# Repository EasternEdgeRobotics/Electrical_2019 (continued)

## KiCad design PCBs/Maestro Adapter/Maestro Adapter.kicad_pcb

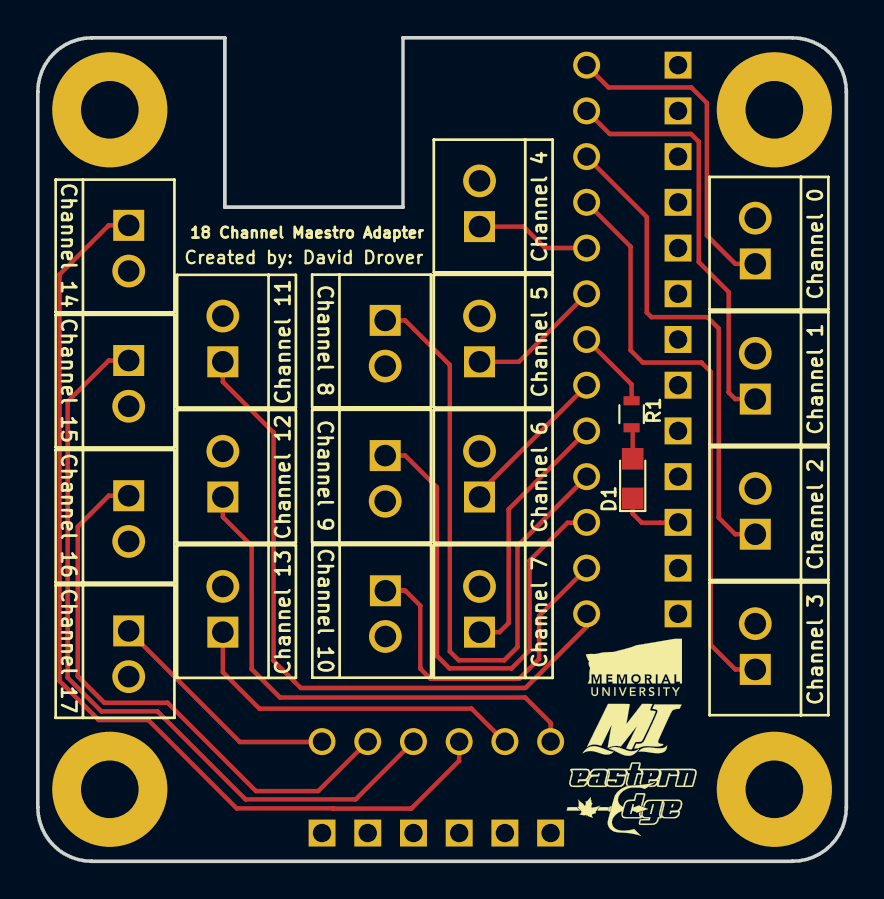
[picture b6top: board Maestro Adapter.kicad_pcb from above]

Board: 2 copper layers, 44.9 x 45.8 mm, 21 parts (0 on the bottom side), 21 nets.

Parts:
18 Channel Maestro: 18ChannelMaestro
Channel 0, Channel 1, Channel 2, Channel 3, Channel 4, Channel 5, Channel 6, Channel 7, Channel 8, Channel 9, Channel 10, Channel 11, Channel 12, Channel 13, Channel 14, Channel 15, Channel 16, Channel 17: 1x2_molex_llc
D1: LED; LED_0805
R1: R; R_0603

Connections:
+5V: 18 Channel Maestro.7, R1.1
GND: 18 Channel Maestro.20, 18 Channel Maestro.21, 18 Channel Maestro.22, 18 Channel Maestro.23, 18 Channel Maestro.24, 18 Channel Maestro.25, 18 Channel Maestro.26, 18 Channel Maestro.27, 18 Channel Maestro.28, 18 Channel Maestro.29, 18 Channel Maestro.30, 18 Channel Maestro.31, 18 Channel Maestro.32, 18 Channel Maestro.33, 18 Channel Maestro.34, 18 Channel Maestro.35, 18 Channel Maestro.36, 18 Channel Maestro.37, 18 Channel Maestro.38, Channel 0.2, Channel 1.2, Channel 2.2, Channel 3.2, Channel 4.2, Channel 5.2, Channel 6.2, Channel 7.2, Channel 8.2, Channel 9.2, Channel 10.2, Channel 11.2, Channel 12.2, Channel 13.2, Channel 14.2, Channel 15.2, Channel 16.2, Channel 17.2, D1.1
unnamed: D1.2, R1.2
unnamed: 18 Channel Maestro.1, Channel 0.1
unnamed: 18 Channel Maestro.2, Channel 1.1
unnamed: 18 Channel Maestro.12, Channel 10.1
unnamed: 18 Channel Maestro.13, Channel 11.1
unnamed: 18 Channel Maestro.14, Channel 12.1
unnamed: 18 Channel Maestro.15, Channel 13.1
unnamed: 18 Channel Maestro.16, Channel 14.1
unnamed: 18 Channel Maestro.17, Channel 15.1
unnamed: 18 Channel Maestro.18, Channel 16.1
unnamed: 18 Channel Maestro.19, Channel 17.1
unnamed: 18 Channel Maestro.3, Channel 2.1
unnamed: 18 Channel Maestro.4, Channel 3.1
unnamed: 18 Channel Maestro.5, Channel 4.1
unnamed: 18 Channel Maestro.6, Channel 5.1
unnamed: 18 Channel Maestro.8, Channel 6.1
unnamed: 18 Channel Maestro.9, Channel 7.1
unnamed: 18 Channel Maestro.10, Channel 8.1
unnamed: 18 Channel Maestro.11, Channel 9.1

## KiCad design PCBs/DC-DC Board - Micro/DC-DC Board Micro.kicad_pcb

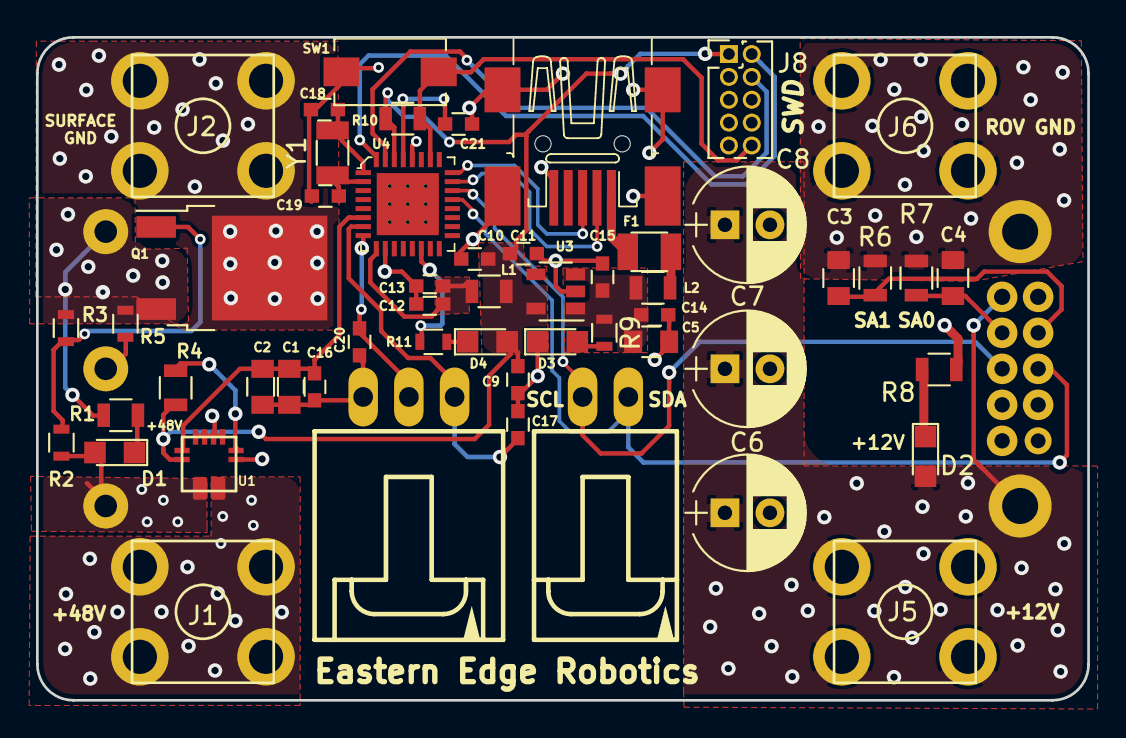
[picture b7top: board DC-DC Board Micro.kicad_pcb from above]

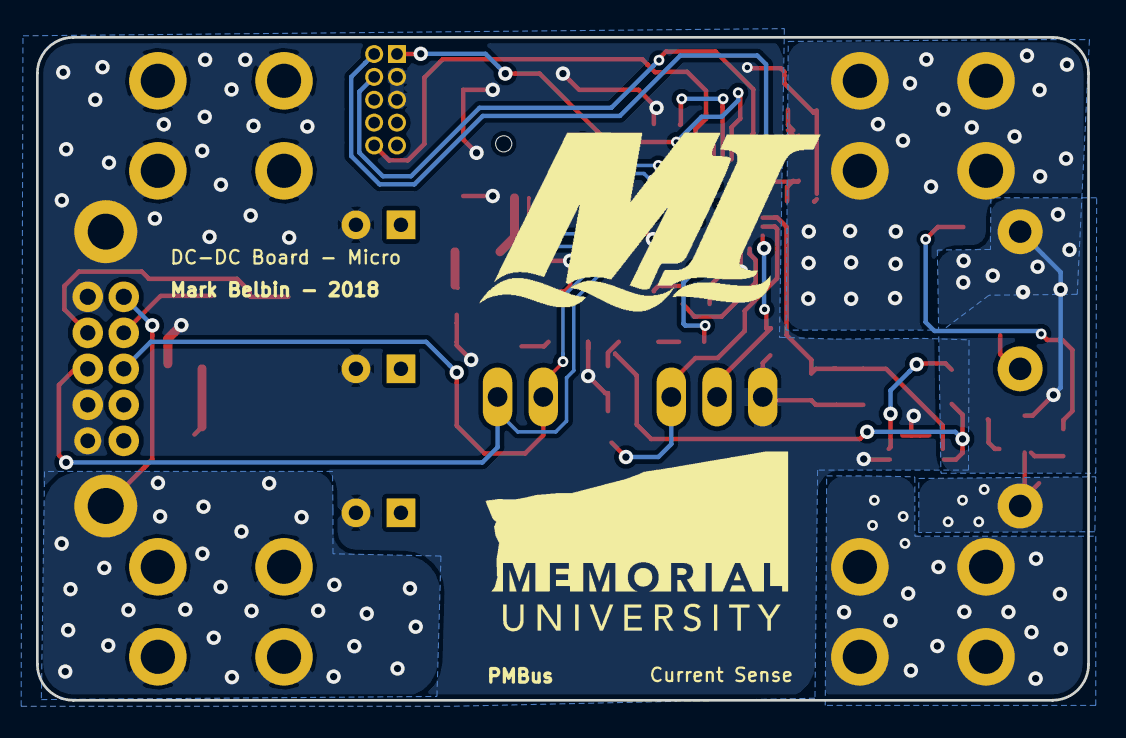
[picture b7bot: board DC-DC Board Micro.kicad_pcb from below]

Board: 2 copper layers, 58.4 x 36.8 mm, 56 parts (2 on the bottom side), 34 nets.

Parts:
C1, C5: 1uF; C_0805
C2: 0.1uF; C_0805
C3, C4: 4.7nF; C_0805
C6: 47uF; CP_Radial_D6.3mm_P2.50mm
C7, C8: 220uF; CP_Radial_D6.3mm_P2.50mm
C9, C12, C14: 10uF; C_0603
C10, C15, C16, C17, C20: 1uF; C_0603
C11, C13, C21: 0.1uF; C_0603
C18, C19: 22pF; C_0603
D1: GRN; LED_0805
D2: BLUE; LED_0805
D3: RED; LED_0805
D4: ORNGE; LED_0805
F1: 500mA; Fuse_SMD1206_Reflow
J1, J2, J5, J6: Conn_01x01; RingTerminal
J3: Conn_01x02; 70553-02
J4: Conn_01x03; 70553-03
J7: USB_B_Mini; 32005-201
J8: Conn_02x05_Odd_Even; Pin_Header_Straight_2x05_Pitch1.27mm
L1, L2: Ferrite_Bead; L_0805
Q1: Q_NMOS_GDS; TO-252-2
R1, R10: 10k; R_0805
R2: 698k; R_0603
R3: 200k; R_0603
R4, R8: 1k; R_0805
R5: 0; R_0603
R6, R7: 0; R_0805
R9: 330; R_0603
R11: 150; R_0603
SW1: SW_Push; SW_SPST_EVQPE1
U1: ACS711
U2: DBQ0135V2; MurataDC-DC
U3: TLV733P; SOT-23-5
U4: ATSAMD21E16L-MFT; QFN-32-1EP_5x5mm
U$15: MUNLOGO
U$16: MILOGO
Y1: 32.7680kHz; Crystal_SMD_3215-2pin_3.2x1.5mm

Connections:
3V3_FILT: C12.1, C13.1, L1.1, U4.9
+3V3: C9.1, C10.1, C11.1, D4.2, J8.1, L1.2, R4.1, R10.1, U1.12, U3.5, U4.30
+5V: C5.1, C14.1, C15.1, L2.1, R9.1, U3.1, U3.3
+12V: C6.1, C7.1, C8.1, D2.2, J5.1, U2.6, U2.16
/+48V: J1.1, U1.3
Earth: Q1.3, R1.2, R3.2, R5.2, U2.4
GND: C1.2, C2.2, C3.2, C4.2, C5.2, C6.2, C7.2, C8.2, C9.2, C10.2, C11.2, C12.2, C13.2, C14.2, C15.2, C16.2, C17.2, C18.2, C19.2, C20.2, C21.2, D3.1, J4.3, J6.1, J7.5, J7.6, J8.3, J8.5, R6.2, R7.2, R8.2, SW1.1, U1.5, U1.7, U2.5, U2.7, U2.13, U2.15, U3.2, U4.10, U4.28
unnamed: C3.1, R6.1, U2.9
unnamed: C4.1, R7.1, U2.8
unnamed: C18.1, U4.1, Y1.1
unnamed: C19.1, U4.2, Y1.2
unnamed: C21.1, U4.29
unnamed: D1.1, R1.1
unnamed: D1.2, R2.1, U1.1, U2.1
unnamed: D2.1, R8.1
unnamed: D3.2, R9.2
unnamed: D4.1, R11.2
unnamed: F1.1, J7.1
unnamed: F1.2, L2.2
unnamed: J2.1, Q1.2
unnamed: Q1.1, R2.2, R3.1
unnamed: R4.2, U1.6
unnamed: R5.1, U2.2
unnamed: R11.1, U4.14
SCL: J3.2, U2.10, U4.22
SDA: J3.1, U2.11, U4.21
SWCLK: J8.4, U4.31
SWDIO: J8.2, U4.32
USB+: J7.3, U4.24
USB-: J7.2, U4.23
VIOUT1: C1.1, C2.1, C16.1, U1.11, U4.6
VIOUT2: C17.1, J4.1, U4.7
VIOUT3: C20.1, J4.2, U4.8
~RESET~: J8.10, R10.2, SW1.2, U4.26

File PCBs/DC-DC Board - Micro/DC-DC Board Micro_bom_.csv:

Component,Description,Part,References,Value,Footprint,Quantity Per PCB,Datasheet,Status
1,Unpolarized capacitor,C,C11 C13 C21,0.1uF,C_0603,3,1276-1258-1-ND,
2,Unpolarized capacitor,C,C2,0.1uF,C_0805,1,399-1169-1-ND,
3,Unpolarized capacitor,C,C9 C12 C14,10uF,C_0603,3,490-7201-1-ND,
4,Unpolarized capacitor,C,C1 C5,1uF,C_0805,2,399-1284-1-ND,
5,Unpolarized capacitor,C,C10 C15 C16 C17 C20,1uF,C_0603,5,1276-6524-1-ND,
6,Polarised capacitor,CP1,C7 C8,220uF,CP_Radial_D6.3mm_P2.50mm,2,399-13664-ND,
7,Unpolarized capacitor,C,C18 C19,22pF,C_0603,2,311-3925-1-ND,
8,Unpolarized capacitor,C,C3 C4,4.7nF,C_0805,2,399-9092-1-ND,
9,Polarised capacitor,CP1,C6,47uF,CP_Radial_D6.3mm_P2.50mm,1,399-13665-ND,
10,LED generic,LED,D2,BLUE,LED_0805,1,732-4982-1-ND,
11,LED generic,LED,D1,GRN,LED_0805,1,732-4983-1-ND,
12,LED generic,LED,D4,ORNGE,LED_0805,1,160-1413-1-ND,
13,LED generic,LED,D3,RED,LED_0805,1,732-4984-1-ND,
14,"Fuse, generic",Fuse,F1,500mA,Fuse_SMD1206_Reflow,1,507-1075-1-ND,
15,"Generic connector, single row, 01x01, script generated (kicad-library-utils/schlib/autogen/connector/)",Conn_01x01,J1 J2 J5 J6,Conn_01x01,RingTerminal,4,36-7770-ND,
16,"Generic connector, single row, 01x02, script generated (kicad-library-utils/schlib/autogen/connector/)",Conn_01x02,J3,Conn_01x02,70553-02,1,WM4900-ND,
17,"Generic connector, single row, 01x03, script generated (kicad-library-utils/schlib/autogen/connector/)",Conn_01x03,J4,Conn_01x03,70553-03,1,WM4901-ND,
18,"Generic connector, double row, 02x05, odd/even pin numbering scheme (row 1 odd numbers, row 2 even numbers), script generated (kicad-library-utils/schlib/autogen/connector/)",Conn_02x05_Odd_Even,J8,Conn_02x05_Odd_Even,Pin_Header_Straight_2x05_Pitch1.27mm,1,609-3712-ND,
19,USB Mini Type B connector,USB_B_Mini,J7,USB_B_Mini,32005-201,1,151-1206-1-ND,
20,Ferrite bead,Ferrite_Bead,L1 L2,Ferrite_Bead,L_0805,2,490-9706-1-ND,
21,Transistor N-MOSFET with substrate diode (general),Q_NMOS_GDS,Q1,Q_NMOS_GDS,TO-252-2,1,DMTH6004SK3-13DICT-ND,
22,Resistor,R,R5,0,R_0603,1,RMCF0603ZT0R00CT-ND,
23,Resistor,R,R6 R7,0,R_0805,2,RMCF0805FT22K0CT-ND,
24,Resistor,R,R1,10k,R_0805,1,RNCP0805FTD10K0CT-ND,
25,Resistor US symbol,R_US,R10,10k,R_0805,1,RNCP0805FTD10K0CT-ND,
26,Resistor,R,R4 R8,1k,R_0805,2,RNCP0805FTD1K00CT-ND,
27,Resistor,R,R3,200k,R_0603,1,RMCF0603JT200KCT-ND,
28,Resistor US symbol,R_US,R9,330,R_0603,1,RHM330DCT-ND,
29,Resistor US symbol,R_US,R11,680,R_0603,1,RHM680DCT-ND,
30,Resistor,R,R2,698k,R_0603,1,RMCF0603FT698KCT-ND,
31,"Push button switch, generic, two pins",SW_Push,SW1,SW_Push,SW_SPST_EVQPE1,1,401-1707-1-ND,
32,,ACS711,U1,ACS711,ACS711,1,620-1482-1-ND,
33,IC MCU 32BIT 64KB FLASH 48QFN,ATSAMD21E16L-MFT,U4,ATSAMD21E16L-MFT,QFN-32-1EP_5x5mm,1,1611-ATSAMD21E16L-MFTCT-ND,Active
34,,MurataDC-DC,U2,DBQ0135V2,MurataDC-DC,1,S5801-05-ND,
35,"200 mA Low Dropout Voltage Regulator, Fixed Output 1.8V, SOT-23-5",TLV70018_SOT23-5,U3,TLV733P,SOT-23-5,1,296-40673-1-ND,
36,Two pin crystal,Crystal,Y1,32.7680kHz,Crystal_SMD_3215-2pin_3.2x1.5mm,1,887-2605-1-ND,





Component Groups:,36
Component Count:,54
Fitted Components:,54
Number of PCBs:,1
Total components:,54
Schematic Version:,
Schematic Date:,
BoM Date:,2018-11-03 11:54:16 PM
Schematic Source:,D:\ROV 2019\Github\2019\PCBs\DC-DC Board - Micro\DC-DC Board Micro.sch
KiCad Version:,Eeschema (5.0.0)

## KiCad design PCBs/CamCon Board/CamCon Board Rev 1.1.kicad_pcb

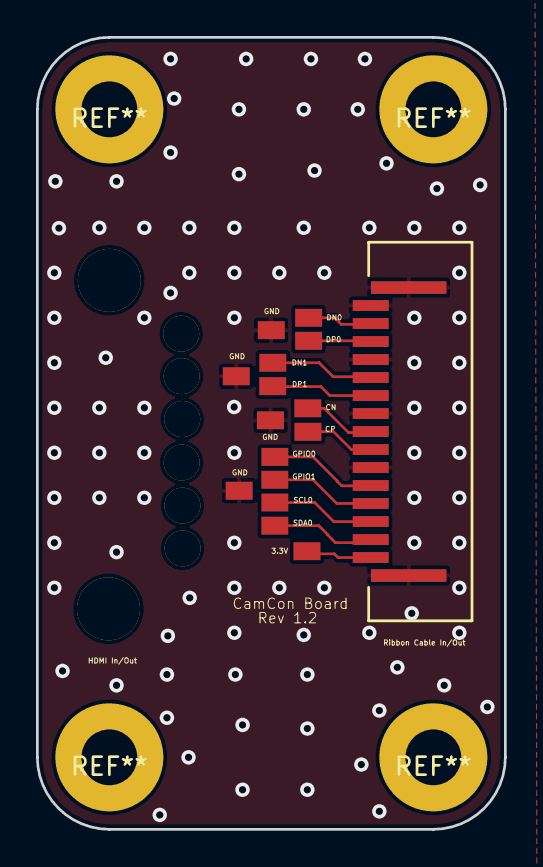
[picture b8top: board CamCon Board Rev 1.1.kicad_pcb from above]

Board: 2 copper layers, 26.0 x 44.0 mm, 25 parts (0 on the bottom side), 12 nets.

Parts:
@HOLE4, @HOLE5, @HOLE6, @HOLE7, @HOLE8, @HOLE9, @HOLE10, @HOLE11: (no value)
J1: SFW15R-1STE1LF; CON15_1X15_DRB_SFW
U$1, U$2, U$3, U$4, U$5, U$6, U$7, U$8, U$9, U$10, U$11, U$12, U$13, U$14, U$15: SOLDERPAD-CAMCON
U$12#2: EERLOGO

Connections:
GND: J1.1, J1.4, J1.7, J1.10, J1.16, J1.17, U$2.P$1, U$4.P$1, U$7.P$1, U$9.P$1
unnamed: J1.2, U$1.P$1
unnamed: J1.3, U$3.P$1
unnamed: J1.5, U$5.P$1
unnamed: J1.6, U$6.P$1
unnamed: J1.8, U$8.P$1
unnamed: J1.9, U$10.P$1
unnamed: J1.11, U$12.P$1
unnamed: J1.12, U$11.P$1
unnamed: J1.13, U$13.P$1
unnamed: J1.14, U$14.P$1
unnamed: J1.15, U$15.P$1

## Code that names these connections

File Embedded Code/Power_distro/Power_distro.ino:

/*************************************/
/*-----------------------------------*/
/**Power Distribution Embedded Code***/
/*****Eastern Edge Robotics 2019******/
/*-----------------------------------*/
/*************************************/

//Contributers: David Drover


//Pin Definitions
#define VIOUT1 2
#define VIOUT2 11
#define VIOUT3 3
#define VIOUT4 10
#define VIOUT5 4
#define VIOUT6 9
#define VIOUT7 5
#define VIOUT8 8
#define VIOUT9 6
#define VIOUT10 7
#define LED 14

float calculateCurrent(int channel, int channelNum);

char hold;
float zeroVoltage [10] = {1625.02,  //channel 1 zero amp voltage
                          1628.64,  //channel 2 zero amp voltage
                          1630.66,  //channel 3 zero amp voltage
                          1630.66,  //channel 4 zero amp voltage
                          1632.28,  //channel 5 zero amp voltage
                          1632.66,  //channel 6 zero amp voltage
                          1636.50,  //channel 7 zero amp voltage
                          1634.69,  //channel 8 zero amp voltage
                          1633.66,  //channel 9 zero amp voltage
                          1650.0}; //channel 10 zero amp voltage

void setup() 
{
  pinMode(VIOUT1, INPUT);
  pinMode(VIOUT2, INPUT);
  pinMode(VIOUT3, INPUT);
  pinMode(VIOUT4, INPUT);
  pinMode(VIOUT5, INPUT);
  pinMode(VIOUT6, INPUT);
  pinMode(VIOUT7, INPUT);
  pinMode(VIOUT8, INPUT);
  pinMode(VIOUT9, INPUT);
  pinMode(VIOUT10, INPUT);
  pinMode(LED, OUTPUT);
  Serial.begin(115200);
  analogReadResolution(12); // sets the ADC to 12 bit mode
}

void loop() 
{
  digitalWrite(LED, HIGH); //so LED won't start being on
  hold = Serial.read();
  while(hold == -1)
  {
    hold = Serial.read();
  }
  if(hold > -1 and hold < 255)
  {
    digitalWrite(LED, LOW); // signal data is starting to be sent
    
    //Serial.print("{ ");
    
    //Serial.print("fore-star-horz:");
    Serial.print(calculateCurrent(VIOUT1,1));
    
    //Serial.print(", fore-port-horz:");
    Serial.print(",");
    Serial.print(calculateCurrent(VIOUT2,2));
    
    //Serial.print(", fore-star-vert:");
    Serial.print(",");
    Serial.print(calculateCurrent(VIOUT3,3));
    
    //Serial.print(", aft-star-horz:");
    Serial.print(",");
    Serial.print(calculateCurrent(VIOUT4,4));
    
    //Serial.print(", fore-port-vert:");
    Serial.print(",");
    Serial.print(calculateCurrent(VIOUT5,5));
    
    //Serial.print(", aft-port-vert:");
    Serial.print(",");
    Serial.print(calculateCurrent(VIOUT6,6));
    
    //Serial.print(", aft-star-vert:");
    Serial.print(",");
    Serial.print(calculateCurrent(VIOUT7,7));
    
    //Serial.print(", aft-port-horz:");
    Serial.print(",");
    Serial.print(calculateCurrent(VIOUT8,8));
    
    //Serial.print(", PI/Switch/Tooling:");
    Serial.print(",");
    Serial.print(calculateCurrent(VIOUT9,9));

    //current chip not installed on pcb
    /*Serial.print(", Blank:");
    Serial.print(calculateCurrent(VIOUT10,10));*/
  
    //Serial.println(" }");
    
    delay(100);
    digitalWrite(LED, HIGH); //signals data is done being sent
  }
}


float calculateCurrent(int channel, int channelNum)
{
  int raw = analogRead(channel);
  float voltage = (raw / 4096.0) * 3300.0; // Gets you mV
  float amps = ((voltage - zeroVoltage[(channelNum - 1)]) / 45.0); //45mv/A
  return amps;
}

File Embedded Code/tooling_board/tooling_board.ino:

/*************************************/
/*-----------------------------------*/
/********Tooling Embedded Code********/
/*****Eastern Edge Robotics 2019******/
/*-----------------------------------*/
/*************************************/

// Contributers: David Drover

#include <Adafruit_Sensor.h> // imu
#include <Adafruit_BNO055.h> // imu
#include <utility/imumaths.h> // imu
#include "MS5837.h" // Pressure
#include <OneWire.h> // Temperature
#include <DallasTemperature.h>// Temperature
#include <Wire.h> // i2c
#include "wiring_private.h" // i2c

// Pin Definitions
#define VMetal 4
#define VPH A5
#define TempData 10
#define EnableA1 9
#define DirA1 14
#define EnableA2 15
#define DirA2 17
#define EnableB1 8
#define DirB1 16
#define EnableB2 19
#define DirB2 28
#define LED 18
#define LED_IN 11
#define SCL_Pin 23
#define SDA_Pin 22

// Global variables
int id;
int dir, dir1, dir2, dir3, dir4; 
int duty, duty1, duty2, duty3, duty4;
int LedDuty;
int tempPH = 0;
int mDetect = 0;
char buf[90];
char hold;
int x;
imu::Vector<3> euler; //primary sensors
imu::Vector<3> accel; //primary sensors
float Temp; //primary sensors
bool gyroSen = true; // Testing gyro
bool pressureSen = true; // Testing pressure
int motors[4] = {EnableA2, EnableB2, EnableA1, EnableB1}; //motors
int dirControl[4] = {DirA2, DirB2, DirA1, DirB1}; //motors
float temperature; // temperature sensor
int rawAvg; // pH sensor
float pH; // pH sensor

// Define one wire communication
OneWire oneWire(TempData);

// Define temperature sensor
DallasTemperature temp(&oneWire);

// Define pressure sensor
MS5837 sensor;

// Define Gyro sensor
Adafruit_BNO055 bno = Adafruit_BNO055();

void returnImuPressureData(int mode = 1);
void changeMotor(int motorNum, int dir, int duty);
void Led(int duty);
void returnSensorData(void);
float calculateTemp(void);
int metal(void);
float ph(double offset);

void setup(void) 
{
  pinPeripheral(11, PIO_TIMER_PWM);
  pinPeripheral(18, PIO_TIMER_PWM);
  pinPeripheral(19, PIO_TIMER_PWM);
  pinPeripheral(22, PIO_SERCOM);
  pinPeripheral(23, PIO_SERCOM);

  analogReadResolution(12); // Sets the ADC to 12 bit mode
  
  Serial.begin(115200);

  if(!sensor.init())
  {
    pressureSen = false;
  }
  
  sensor.setModel(MS5837::MS5837_02BA);
  sensor.setFluidDensity(997);
  
  if(!bno.begin())
  {
    gyroSen = false;
  }

  temp.begin();

  // Setup pins
  pinMode(VMetal, INPUT); 
  pinMode(VPH, INPUT); 
  pinMode(TempData, INPUT); 
  pinMode(EnableA1, OUTPUT);
  pinMode(DirA1, OUTPUT);
  pinMode(EnableA2, OUTPUT);
  pinMode(DirA2, OUTPUT);
  pinMode(EnableB1, OUTPUT);
  pinMode(DirB1, OUTPUT);
  pinMode(EnableB2, OUTPUT);
  pinMode(DirB2, OUTPUT);
  pinMode(LED, OUTPUT);
  pinMode(LED_IN, OUTPUT);
  
  // Ensure nothing run from not being set
  for(int i = 1; i<=4; i++)
  {
    changeMotor(i, 1, 0);
  }
  Led(0);
  for(int i = 0; i < 90; i++)
  {
    buf[i]= ',';
  }
}

void loop(void) 
{
  // Waiting for a serial write
  hold = Serial.read();
  while(hold == 255)
  {   
    if(tempPH == 1 or mDetect == 1)
    {
      returnSensorData();
    }
    else
    {
      if(gyroSen == false)
      {
        Serial.print("gyro not found");
        Serial.flush();
      }
      if(pressureSen == false)
      {
        Serial.print("pressure not found");
        Serial.flush();
      }
      returnImuPressureData();
    }
    hold = Serial.read(); 
  }

  // Serial reading code
  buf[0] = hold;
  x = 1;
  while(x <= 30 and hold != 255)
  {
    delay(4);
    hold = Serial.read();
    while( x == 0 and hold == 255)
    {
      hold = Serial.read();
    }
    buf[x] = hold;
    x++;
  }

  // Decides how to read the input and does the action

  if(buf[2] == 'm' and buf[7] == '1')
  {
    sscanf(buf, "{ motor1:%d, %d, motor2:%d, %d, motor3:%d, %d, motor4:%d, %d, LED:%d, sensorsreading:%d,%d }", &dir1, &duty1, &dir2, &duty2, &dir3, &duty3, &dir4, &duty4, &LedDuty, &tempPH , &mDetect);
    changeMotor(1, dir1, duty1);
    changeMotor(2, dir2, duty2);
    changeMotor(3, dir3, duty3);
    changeMotor(4, dir4, duty4);
    Led(LedDuty);
  }else if(buf[2] == 'm'){
    sscanf(buf, "{ motor:%d, %d, %d }", &id, &dir, &duty);
    changeMotor(id, dir, duty);
  }else if(buf[2] == 'L'){
    sscanf(buf, "{ LED:%d }", &LedDuty);
    Led(LedDuty);
  }else if(buf[2] == 's'){
    sscanf(buf, "{ sensorsreading:%d,%d }", &tempPH , &mDetect);
  }else{
    sscanf(buf, "%d,%d,%d,%d,%d,%d,%d,%d,%d,%d,%d", &dir1, &duty1, &dir2, &duty2, &dir3, &duty3, &dir4, &duty4, &LedDuty, &tempPH, &mDetect);
    changeMotor(1, dir1, duty1);
    changeMotor(2, dir2, duty2);
    changeMotor(3, dir3, duty3);
    changeMotor(4, dir4, duty4);
    Led(LedDuty);
  }
}


// Prints out imu and pressure sensors data
void returnImuPressureData(int mode)
{
  sensor.read();
  euler = bno.getVector(Adafruit_BNO055::VECTOR_EULER);
  accel = bno.getVector(Adafruit_BNO055::VECTOR_LINEARACCEL);
  Temp = bno.getTemp();

  Serial.print("P");
  Serial.flush();

  //Serial.print("Pressure:");
  Serial.print(",");
  Serial.flush();
  Serial.print(sensor.pressure());
  Serial.flush(); 
  
  //Serial.print(", TemperaturePS:"); 
  Serial.print(",");
  Serial.flush();
  Serial.print(sensor.temperature());
  Serial.flush(); 
 
  //Serial.print(", GyroX:");
  Serial.print(",");
  Serial.flush();
  Serial.print(euler.x());
  Serial.flush();
  
  //Serial.print(", GyroY:");
  Serial.print(",");
  Serial.flush();
  Serial.print(euler.y());
  Serial.flush();
  
  //Serial.print(", GyroZ:");
  Serial.print(",");
  Serial.flush();
  Serial.print(euler.z());
  Serial.flush();

  //Serial.print(", Accelx:");
  Serial.print(",");
  Serial.flush();
  Serial.print(accel.x());
  Serial.flush(); 

  //Serial.print(", Accely:");
  Serial.print(",");
  Serial.flush();
  Serial.print(accel.y());
  Serial.flush(); 

  //Serial.print(", Accelz:");
  Serial.print(",");
  Serial.flush();
  Serial.print(accel.z());
  Serial.flush(); 

  //Serial.print(", TemperatureIMU:");
  Serial.print(",");
  Serial.flush();
  Serial.println(Temp);
  Serial.flush();
}

// Changes motor turn speed
void changeMotor(int motorNum, int dir, int duty)
{
  //if(motorNum == 2)
  //{
  //  motorNum--;
  //  digitalWrite(dirControl[motorNum], dir);
  //  digitalWrite(motors[motorNum], (1.0*(duty/100.0)));
  //}
  //else
  //{
    motorNum--;
    digitalWrite(dirControl[motorNum], dir);
    analogWrite(motors[motorNum], (256.0*(duty/100.0)));
  //}
}

// Changes the brightness of the leds
void Led(int duty)
{
  duty = (256.0 *(duty / 100.0));
  analogWrite(LED, duty);
  analogWrite(LED_IN, (256 - duty));
}

// Prints out ph, metal and temperature sensor values
void returnSensorData(void)
{
  Serial.print("S");
  Serial.flush();
  
  //Serial.print("temperature:");
  Serial.print(",");
  Serial.flush();
  if(tempPH == 1)
  {
    Serial.print(calculateTemp());
    Serial.flush();
  }else{
    Serial.print("F");
    Serial.flush();
  }
  
  //Serial.print(", Metal:");
  Serial.print(",");
  Serial.flush();
  if(mDetect == 1)
  {
    Serial.print(metal());
    Serial.flush();
  }else{
    Serial.print("F");
    Serial.flush();
  }
  
  //Serial.print(", PH:");
  Serial.print(",");
  Serial.flush();
  if(tempPH == 1)
  {
    Serial.println(ph(2.72));
    Serial.flush();
  }else{
    Serial.println("F");
    Serial.flush();
  }
}

// Calculates temperature
float calculateTemp(void)
{
  delay(40);
  temp.requestTemperatures();
  delay(40);
  temperature = temp.getTempCByIndex(0);
  return temperature;
}

// Says if it is metal or not
int metal(void)
{
  if(analogRead(VMetal) < 100 )
  {
    return 1;
  }
  else
  {
    return 0;    
  }  
}

// Calculates ph level
float ph(double offset)
{
  rawAvg = 0;
  for( int i = 0; i < 4; i++)
  {
    rawAvg += analogRead(VPH);
    delay(5);
  }
  rawAvg /= 4;
  pH = ((3.5 * (rawAvg * (3.3 / 4096.0))) + offset);
  return pH;
}

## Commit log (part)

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2018-09-23 Added Bar02 Files
    Blue Robotics open-sourced their Bar02 PCB files. We could use this to reduce the Bar02 cost by over half
2018-09-23 Added CamCon Board PCB
    This board, which will be improved upon a little further, will serve as a bridge between the Pi's ribbon cables and an HDMI cable.
2018-09-23 Update README.md
    Added mention of PCBs
2018-09-24 Added Legacy Junction Box
    Added all my Junction Box stuff since it might come in handy
2018-09-24 Added BR Bar02 Library
    Arduino library for the pressure sensor in the Bar02. We can easily port this over to another micro when we need to, it's just a bunch of I2C commands.
2018-09-29 Played with 3D Models
    Tried out a few thngs with 3D models for components. Apparently the new KiCAD takes STEP files which is a huge time saver!!
2018-09-30 Cleaned up CamCon Board
2018-10-07 Started New CamCon Board
    Mostly sourced components and updated the EER library.
2018-10-07 Revert "Started New CamCon Board"
    This reverts commit b871feee2390acae07443b14e396deeaba97d5d0.
2018-10-07 Revert "Revert "Started New CamCon Board""
    This reverts commit 2fa29a33d9c013c2d74e11c9c642eee02ae13c05.
2018-10-07 Think everything's chill now
2018-10-07 Finished Mechanicals of the Dual CamCon Board
    Just need to do the routing now.
2018-10-08 Dual CamCon Board - Ready for Review
    Pretty much cleaned up this guy as much as I could. Needs to be reviewed by the team on a few different things.
    -FPC to HDMI legitness (will each pin line up) needs to be triple checked.
2018-10-10 Major Routing Fix for Dual CamCon
    After looking at the physical Pi Cam I realized that I had the pin map mirrored. I swapped the pins around on the FPC connector and cleaned up the board in general. Count this as a double check, stil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
2018-10-11 Touched up Dual CamCon
2018-10-13 Semi Final DC-DC Schematic
    Pretty much finalized the schematic and component selection for the no-micro version of the DC-DC board. The micro version will come later.
2018-10-15 DC-DC Board Final
    99% Done the first DC-DC Board. Just need to double check everything!!
2018-10-15 DC-DC Touchups
    Silk screen mostly
2018-10-16 Fixed DC-DC
    After looking at the IRL DC-DCs, I realized I had the footprint mirrored (the datasheet is not intuitive). I rerouted pretty much everything to fix it. RIP
2018-10-17 DC-DC Board DONE
    Should be done for sure now bys
2018-10-17 DC-DC Touchups
    Small layout touchups. Also double checked the reverse voltage protection in LTSpice, and it looks good!!! <1W of power dissipation!!
2018-10-19 Cleaned up BOM
    KiCAD has a built in BOM!! Woohooo!!!
2018-10-20 Started DC-DC with Micro
    Picked out microcontroller maybe? Still gotta decide if I want to use the 5x5 vs the 7x7.
2018-10-20 Added Datasheets
    Figured this would be useful to have on the Github
2018-10-20 Started Blank Project
    Commit all you can guys, also pull down what's been done.
2018-10-20 Added Blank Project
    Commit, commit, commit!!
2018-10-20 Added Blank Project
    Commit boyz
2018-10-21 DC-DC Mirco Updates
2018-10-22 DC-DC Boards 99%
    Both boards are pretty much done. They just need a few double checks and some BOM work has to be done for the Micro Board.
2018-10-23 DC-DC Micro Touchups
    Cleaned up layout and fixed orange test LED current limiting resistor.
2018-10-23 finished rough draft of Maestro Adapter
    3d model and EER silkscreen is done.
2018-10-23 added spot for missed gap in servo channels
    missed a gap between channel 5 and 6. so added additional pads
2018-10-24 Added Colour to 3D Model
    We probably have to change the footprint again anyways, but at least now its in colour!!!
2018-10-24 DC-DC Micro FINAL*
    Checked it over fully, gonna call this board finished now unless anyone else has a concern!
2018-10-24 Added another 3d model path
2018-10-25 Converting to 18 channel maestro
2018-10-25 Finished pcb Layout
2018-10-25 Finished traces
2018-10-26 Changed the mounting holes
2018-10-26 Revert "DC-DC Micro FINAL*"
    This reverts commit 0ab9bedbdf57a5134aa5828bf11276fde0e8bb90.
2018-10-26 Edited Paths for 3D Models
    This might fix an issue me and Patrick found. The paths for 3D models were absolute referenced as if it were on my computer. It's obviously fine for me, but not for everyone else loll. Hopefully the 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
2018-10-26 Move maestro to the bottom and move connectors
2018-10-26 added relative path for 3d models
2018-10-27 Added traces and rounded corners
    mounting hole centers are 4mm from the side
2018-10-27 Started Power Distro Board
    Started the schematic of the power distribution board (12V and GND bus). This will mostly be copy/paste, the hard part will come in the layout.
2018-10-27 Added EER logo silkscreen
2018-10-27 Added led and resistor pads
2018-10-27 Added text EER and year
2018-10-27 Schematic Finalized
    99% done on the schematic, just needs to be checked over and touched-up.
2018-10-29 BOM Finished Pwr Distro
    Finished the BOM (Bill of Materials) for the Power Distribution Board. Also the schematic is finalized for sure.
2018-10-29 Initial Component Position PD
    Placed initial component position. I'm going to bed.
2018-10-31 Small Tweaks
    3D Model for RPi GPIO on the CamCon was wrong.
2018-11-03 Updated Silkscreen PD
    Still need to check over the layout one last time, but she should be good to go.
2018-11-03 I'm sorry Keith
    It had to be done....
2018-11-03 finished motor driver circuit
2018-11-03 Finished PD Board
    All done!
2018-11-03 Started Relay
    finish relay values
2018-11-03 BOM Work
2018-11-03 Gerber Generation
    Oops should not have done this in the actuator branch but here we are loll. Just exported the gerber files for the DCDC / DCDC Micro & the PD Board. Should not affect what you guys are doing.
2018-11-04 Added CamCon Gerbers
    Need to fix these up loll
2018-11-04 Gerbers and Maestro Fix
    Added Gerbers for the maestro and fixed up the silkscreen.
2018-11-04 Minor Updates
    Trying to sneak these Power PCBs through PCBWay, they caught me on a few 0.2mm drills so I made em 0.3. We'll see if my 0.2mm clearance passes their 8mil clearance (0.2035mm)
2018-11-04 Added motor diver schematic and relay footprint
2018-11-04 More Gerbers
2018-11-04 Filled in some information about transistor
2018-11-08 3D Modeling
2018-11-10 reset accidental commit to master
2018-11-12 Updated Mirco Stuff
    Dodged a bullet
2018-11-14 added datasheets to H bridge compoents
2018-11-24 add wiki link to readme for docs
2018-11-25 Created project
2018-11-27 First SAMD21 Program!!
    Using Atmel Studio 7 here since it was the easist to get up and running. Gonna try and program this completely through the Arduino IDE eventually. pls help :)
2018-11-28 Arduino Test
    Got the board working with the Ardunio IDE. Still some testing we gotta do to check if it'll do everything we want (I2C, proper USB communication, analog in / digital out) Promising though :)
2018-12-08 PMBus Works!!
    Got the PMBus working on the DC-DC converters. I'll start making the commands more formalized. The only thing now is to figure out addresses. Worst case scenerio is we can't access 1-2 of the convert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
2019-01-18 Moved Repositories
    Moved my old branch in 2019 repo to this branch.
2019-01-18 Add unedited pressure and imu test code
2019-01-25 Initial Tooling Board
    - Created Project
    - Added Micro Schematic
    - Need to finalize everything else (I'm in for a long night)
2019-01-26 Add DC Motor Control
    -Added H-bridge drivers and logic inverters
    -Should be able to control up to 6 DC motors / other loads
    -We'll see if we can fit 3 chips on the board (we should be able to)
2019-01-26 Finished Actuator Section
    -Added Dual LED Control
    -Spec'd fets for nmos in LED circuit
    -Still need to map all control pins
2019-01-26 Added Sensors
    -Added pH Circuit and spec'd components
    -Added Pressure sensor connecter
    -Added External Temp sensor connector
    -Added metal detector connector + input circuit
    Need to add IMU interface now (not hard)
2019-01-26 Pins are Mapped
    -This was really difficult and it may not work.
    -We're gonna try it and see what works.
    -If it fails the next PCB will use arduino atmega chips since the open source libraries exist for them
    -Might do a combination of SAMD and atmega lol
    -God damn chinese new year
2019-01-26 Added Footprints
    -Whoooo boy here we go
2019-01-26 Removed 3rd DC Motor Driver
    -Can only do 4 DC motors now, not enough board space
2019-01-27 Almost Finished
    -Still going, help
2019-01-27 Just the Micro
    -Need to fricken route the micro help
2019-01-28 Tooling Board Finalized
    -Checked Routing
    -Added 3D models for all components
    -She looks pretty good boys
2019-01-28 ToolingBoard Touch-ups
    -Cleaned up routing
    -Enlarged power traces
    -Fixed return paths on motor ground
2019-01-29 Tooling Gerbs
    -Respun Gerbers
2019-01-30 Created STEP file
2019-01-30 Finished battery pack pcbs
2019-01-31 readded battery pack with boms
2019-01-31 renamed files
2019-02-15 tooling board bom
2019-02-15 embedded code
    code for the power distrobution board is done, the tooling board code is almost done but isn't tested and the i2c scanner is a useful tool when looking at the dc dc code
2019-02-15 modifed DCDC code
    added current reading and serial printing of data for all three DCDC
2019-02-20 added comments to dc dc code
2019-02-26 updated serial read
    updated the wait for a serial message because the samd chip didn't like serial.available
2019-02-26 optimized serial reading
    made the parse faster (used to be 1 second now is 100 milliseconds)
2019-02-27 updated serial reading
    implemented multiple ways to change things on the tooling board
2019-02-28 updated serial read
    updated it to have less of a delay
2019-03-01 created a serial read program
    created a serial read program for depth and pressure sensors values
2019-03-01 added format comment
2019-03-04 added libraries and updated code
    update the dcdc code the power distro code and the imu pressure test bench code, added all libraries need for the tooling broad
2019-03-04 updated serial printing format
    impleamented correct csv format
2019-03-04 updated test code
2019-03-05 added equation
    added equation to calculate ph from the sensor
2019-03-06 added testing program
    added testing program for testing sending comunication with the tooling board
2019-03-07 commented out some other reading formats
    csv is the only enabled reading format
2019-03-10 updated libraries for i2c
    edited libraries to get them to use our i2c pins instead of default i2c pin and cleaned up some tooling board code
2019-03-11 testing the gyro
    fixed i2c issues and testing gyro for function
2019-03-13 updated tooling board and coms
    updated test coms with the board and updated the tooling board by move some variables around and uncommenting sensors
2019-03-13 added finishing feature for testing code
    added and icon to the window for testing
2019-03-13 updated tooling board
2019-03-15 added pin notes
    enable a2 may be on a pin that doesn't support pin modifications
2019-03-15 updated motor control and csv format
    updated motor control on the tooling board. change the json printing format from the power distro board and DCDC board to a csv format
2019-03-16 fixed tooling board
2019-03-17 Switch tooling board testing gui to tk rather than qt
2019-03-17 Fix spelling and style issues with some arduino code
2019-03-18 Fix GUI buttons
2019-03-22 fixed merge issue
2019-03-22 updated pressure and imu test code
    updated the test platforms code
2019-03-22 updated tool board code
    update code for the variant.cpp change
2019-03-23 updated variant
2019-03-23 old version of imu libaraies
2019-03-25 updated board varaint and pin assignment
2019-03-26 PWM on led light pin code and variant
2019-04-01 modifed tool board code
    testing sensor values
2019-04-02 added sensor reading code
2019-04-03 changed acceleration read
    changed from gravity to linear
2019-04-06 updated ph and metal detector code
2019-04-06 tuned sensors
    updated code for sensors
2019-04-12 updated sensor reading
    updated reading to decussed format
